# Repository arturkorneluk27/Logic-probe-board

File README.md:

🇵🇱Polish version
# Próbnik stanów logicznych
  
    Odtworzenie gotowej płytki PCB w programie KiCad na zasadach reverse engineering.
    
# Opis projektu

Podczas laboratorium "Montaż Systemów Elektronicznych" wykonałem ręczny montaż próbnika stanów logicznych
z wykorzystaniem technologii SMD oraz lutowania bezołowiowego.

Po zakończeniu zajęć postanowiłem odtworzyć projekt płytki w programie KiCad.
Na podstawie gotowego urządzenia wykonałem schemat ideowy oraz projekt PCB,
starając się możliwie wiernie odwzorować oryginalny układ, rozmieszczenie
elementów oraz prowadzenie ścieżek.

Projekt miał na celu rozwinięcie umiejętności projektowania schematów i płytek PCB w KiCadzie oraz analizowania działania układów cyfrowych.

# Funkcjonalność 

Próbnik umożliwia wykrycie:
- 🟢 stanu logicznego LOW
- 🔴 stanu logicznego HIGH
- 🔵 zbocza opadającego FALL
- 🟡 zbocza narastającego RISE 
  
Sygnalizacja realizowana jest za pomocą czterech diod LED.

# Zastosowane układy

- LM358 - podwójny wzmacniacz operacyjny pracujący jako komparator napięcia
- HEF4001 / CD4001 - układ czterech bramek NOR

# Narzędzia

- KiCad
- Git / Github

# Etapy projektu

1. Odtworzenie schematu ideowego
2. Dobór symboli i footprintów elementów
3. Zaprojektowanie PCB
4. Odtworzenie rozmieszczenia elementów
5. Odtworzenie przebiegu ścieżek na podstawie fizycznej płytki

# Pliki projektu
- `probnik.kicad_sch` - schemat ideowy
- `probnik.kicad_pcb` - projekt płytki PCB
- `probnik.kicad_pro` - plik projektu KiCad

<br><br>
---

🇬🇧English version

# Logic State Probe

    Recreation of an assembled PCB in KiCad using reverse engineering techniques.

# Project description

During the "Electronic Systems Assembly" lab, I manually assembled
a logic state probe using SMD technology and lead-free soldering.

After completing the lab, I decided to recreate the PCB design in KiCad.
Based on the finished device, I drew the schematic and designed the PCB,
aiming to faithfully reproduce the original circuit, component placement,
and trace routing.

The goal of the project was to develop schematic and PCB design skills
in KiCad and better understand how digital circuits work.

# Features

The probe can detect:
- 🟢 logic LOW state
- 🔴 logic HIGH state
- 🔵 falling edge FALL
- 🟡 rising edge RISE

Each state is visualised by a dedicated LED.

# Components used

- LM358 - dual op-amp operating as a voltage comparator
- HEF4001 / CD4001 - quad NOR gate IC

# Tools

- KiCad
- Git / Github

# Project stages
1. Recreating the schematic
2. Selecting symbols and footprints
3. Designing the PCB layout
4. Reconstructing component placement
5. Reconstructing PCB trace routing based on the physical board

# Project files
- `probnik.kicad_sch` - schematic
- `probnik.kicad_pcb` - PCB layout
- `probnik.kicad_pro` - KiCad project file

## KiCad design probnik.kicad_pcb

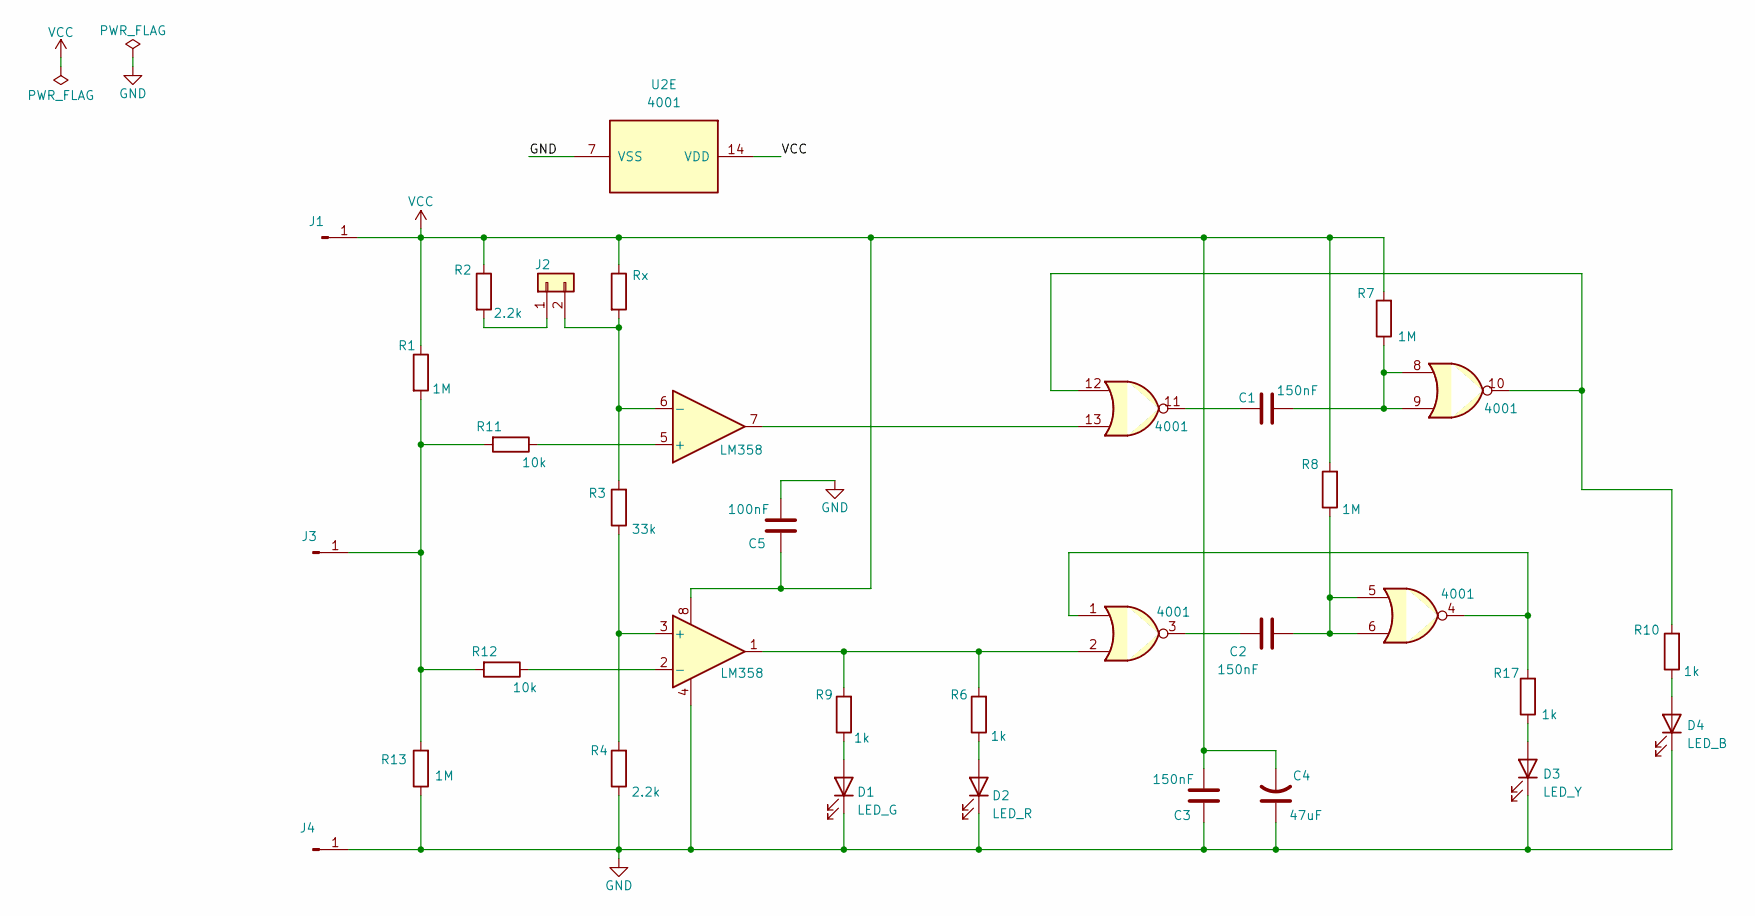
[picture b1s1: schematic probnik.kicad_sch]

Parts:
C1, C2, C3: 150nF; C_0603_1608Metric
C4: 47uF; CP_Elec_3x5.3
C5: 100nF; C_0603_1608Metric
D1: LED_G; LED_0603_1608Metric
D2: LED_R; LED_0603_1608Metric
D3: LED_Y; LED_0603_1608Metric
D4: LED_B; LED_0603_1608Metric
J1, J4: Conn_01x01_Pin; PinHeader_1x01_P2.54mm_Vertical
J2: Conn_01x02; PinHeader_1x02_P2.54mm_Vertical
J3: Conn_01x01_Pin; TestPoint_Pad_D2.0mm
R1, R7, R8, R13: 1M; R_0603_1608Metric
R2, R4: 2.2k; R_0603_1608Metric
R3: 33k; R_0603_1608Metric
R5: Rx; R_0603_1608Metric
R6, R9, R10, R17: 1k; R_0603_1608Metric
R11, R12: 10k; R_0603_1608Metric
U1: LM358; SOIC-8_3.9x4.9mm_P1.27mm
U2: 4001; SOIC-14_3.9x8.7mm_P1.27mm

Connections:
GND: C3.2, C4.1, C5.2, D1.1 (K), D2.1 (K), D3.1 (K), D4.1 (K), J4.1, R4.1, R13.1, U1.4 (V-), U2.7 (VSS)
unnamed: C1.1, U2.11
unnamed: C1.2, R7.1, U2.8, U2.9
unnamed: C2.1, U2.3
unnamed: C2.2, R8.1, U2.5, U2.6
unnamed: D1.2 (A), R9.1
unnamed: D2.2 (A), R6.1
unnamed: D3.2 (A), R17.1
unnamed: D4.2 (A), R10.1
unnamed: J2.1, R2.2
unnamed 10: J2.2, R3.2, R5.2, U1.6 (-); also elsewhere on the board
unnamed: J3.1, R1.2, R11.2, R12.2, R13.2
unnamed: R6.2, R9.2, U1.1, U2.2
unnamed: R10.2, U2.10, U2.12
unnamed: R17.2, U2.1, U2.4
unnamed: U1.7, U2.13
unnamed: R3.1, R4.2, U1.3 (+)
unnamed: R12.1, U1.2 (-)
unnamed: R11.1, U1.5 (+)
VCC: C3.1, C4.2, C5.1, J1.1, R1.1, R2.1, R5.1, R7.2, R8.2, U1.8 (V+), U2.14 (VDD); also elsewhere on the board

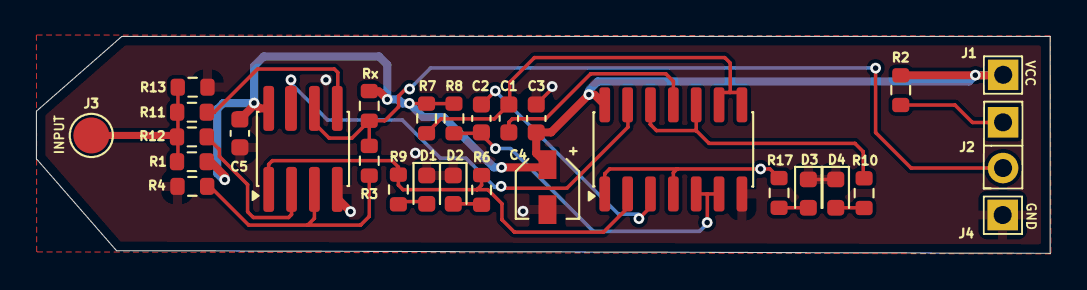
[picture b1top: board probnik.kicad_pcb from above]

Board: 2 copper layers, 56.3 x 12.0 mm, 29 parts (0 on the bottom side), 20 nets.

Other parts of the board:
Rx: Rx; R_0603_1608Metric

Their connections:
unnamed 10: Rx.2; also elsewhere on the board
VCC: Rx.1; also elsewhere on the board

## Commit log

2026-06-08 Initial Kicad project
2026-06-08 created README
2026-06-09 added screenshots of the schematic and PCB view
